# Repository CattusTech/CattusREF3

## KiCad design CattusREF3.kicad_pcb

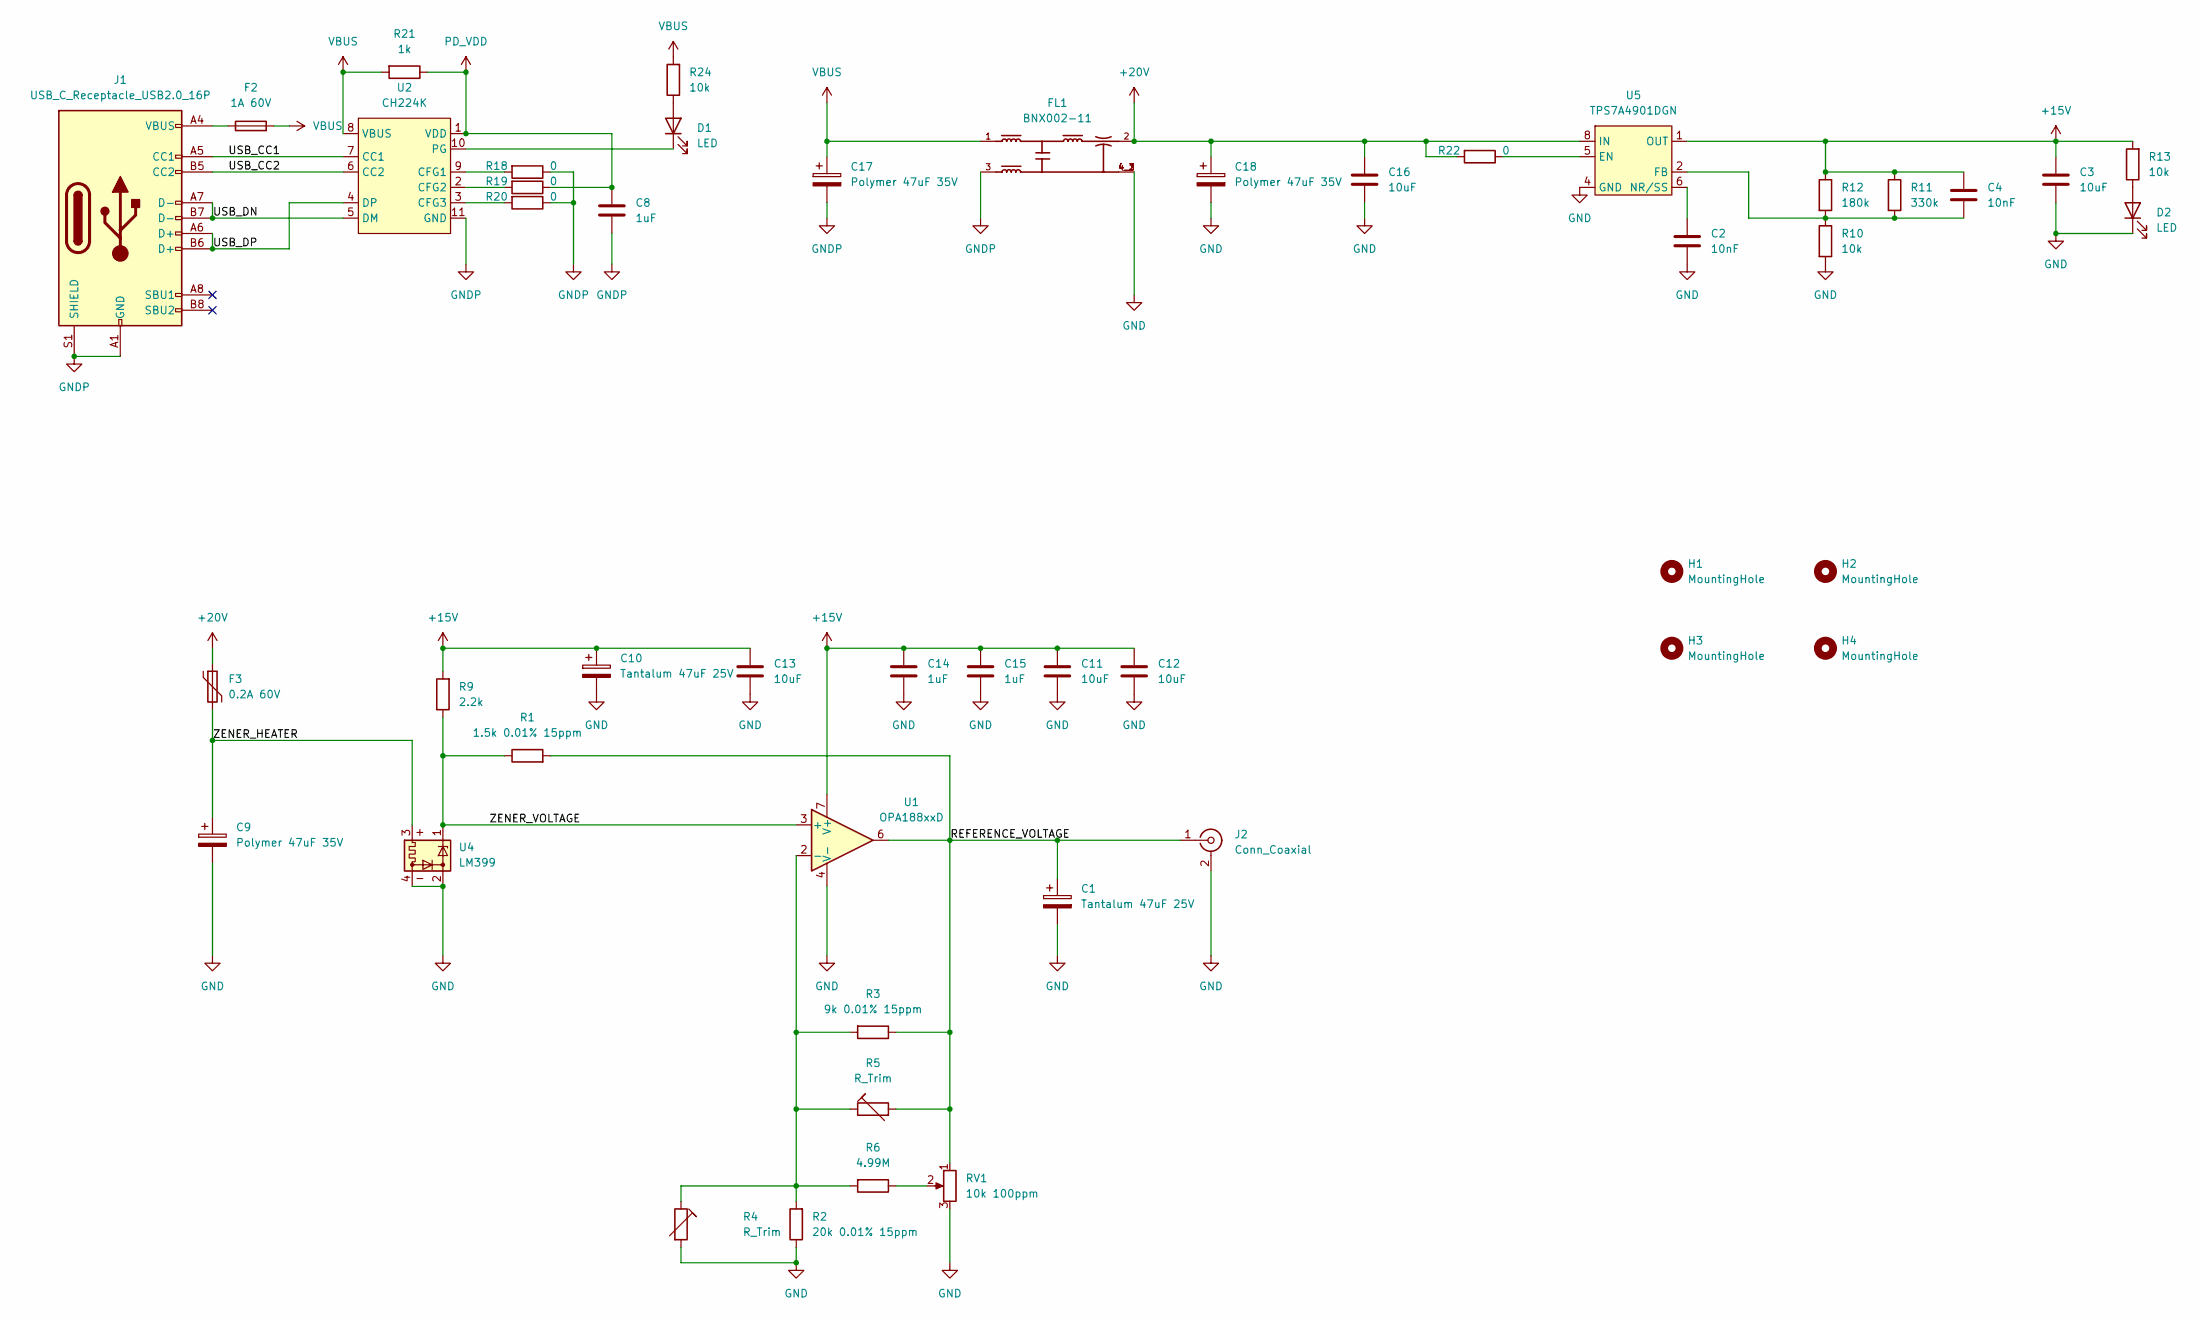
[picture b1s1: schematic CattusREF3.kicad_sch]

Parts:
C1, C10: Tantalum 47uF 25V; CP_EIA-7343-31_Kemet-D
C2, C4: 10nF; C_0603_1608Metric
C3, C11, C12, C13, C16: 10uF; C_0805_2012Metric
C8, C14, C15: 1uF; C_0603_1608Metric
C9, C17, C18: Polymer 47uF 35V; CP_Elec_6.3x7.7
D1, D2: LED; LED_0603_1608Metric
F2: 1A 60V; Fuse_1206_3216Metric
F3: 0.2A 60V; Fuse_1206_3216Metric
FL1: BNX002-11; BNX002; PARTREV N/A
H1, H2, H3, H4: MountingHole; MountingHole_3.2mm_M3_ISO14580
J1: USB_C_Receptacle_USB2.0_16P; USB_C_Receptacle_GCT_USB4105-xx-A_16P_TopMnt_Horizontal
J2: Conn_Coaxial; SMA_Amphenol_901-143_Horizontal
R1: 1.5k 0.01% 15ppm; R_0603_1608Metric
R2: 20k 0.01% 15ppm; R_0603_1608Metric
R3: 9k 0.01% 15ppm; R_0603_1608Metric
R4, R5: R_Trim; R_0603_1608Metric
R6: 4.99M; R_0603_1608Metric
R9: 2.2k; R_0603_1608Metric
R10, R13, R24: 10k; R_0603_1608Metric
R11: 330k; R_0603_1608Metric
R12: 180k; R_0603_1608Metric
R18, R19, R20, R22: 0; R_0603_1608Metric
R21: 1k; R_0603_1608Metric
RV1: 10k 100ppm; Potentiometer_Bourns_3296W_Vertical
U1: OPA188xxD; SOIC-8_3.9x4.9mm_P1.27mm
U2: CH224K; SSOP-10-1EP_3.9x4.9mm_P1mm_EP2.1x3.3mm
U4: LM399; Analog_TO-46-4_ThermalShield
U5: TPS7A4901DGN; Texas_DGN0008B_VSSOP-8-1EP_3x3mm_P0.65mm_EP2x3mm_Mask1.88x1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

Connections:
+15V: C3.2, C4.2, C10.1, C11.2, C12.2, C13.2, C14.2, C15.2, R9.2, R11.1, R12.1, R13.2, U1.7 (V+), U5.1 (OUT)
+20V: C16.2, C18.1, F3.1, FL1.2, R22.2, U5.8 (IN)
/REFERENCE_VOLTAGE: C1.1, J2.1 (In), R1.2, R3.1, R5.2, RV1.1, U1.6
/USB_CC1: J1.A5 (CC1), U2.7 (CC1)
/USB_CC2: J1.B5 (CC2), U2.6 (CC2)
/USB_DN: J1.A7 (D-), J1.B7 (D-), U2.5 (DM)
/USB_DP: J1.A6 (D+), J1.B6 (D+), U2.4 (DP)
/ZENER_HEATER: C9.1, F3.2, U4.3
/ZENER_VOLTAGE: R1.1, R9.1, U1.3 (+), U4.1
GND: C1.2, C2.1, C3.1, C9.2, C10.2, C11.1, C12.1, C13.1, C14.1, C15.1, C16.1, C18.2, D2.1 (K), FL1.4_1, FL1.4_2, FL1.4_3, J2.2 (Ext), R2.1, R4.2, R10.2, RV1.3, U1.4 (V-), U4.2, U4.4, U5.4 (GND), U5.9 (GND)
GNDP: C8.1, C17.2, FL1.3, J1.A1 (GND), J1.A12 (GND), J1.B1 (GND), J1.B12 (GND), J1.S1 (SHIELD), R18.1, R20.1, U2.11 (GND)
unnamed: D1.2 (A), R24.1
unnamed: D1.1 (K), U2.10 (PG)
unnamed: D2.2 (A), R13.1
unnamed: F2.1, J1.A4 (VBUS), J1.A9 (VBUS), J1.B4 (VBUS), J1.B9 (VBUS)
unnamed: R6.1, RV1.2
unnamed: R2.2, R3.2, R4.1, R5.1, R6.2, U1.2 (-)
unnamed: R18.2, U2.9 (CFG1)
unnamed: R19.2, U2.2 (CFG2)
unnamed: R20.2, U2.3 (CFG3)
unnamed: R22.1, U5.5 (EN)
unnamed: C4.1, R10.1, R11.2, R12.2, U5.2 (FB)
unnamed: C2.2, U5.6 (NR/SS)
PD_VDD: C8.2, R19.1, R21.1, U2.1 (VDD)
VBUS: C17.1, F2.2, FL1.1, R21.2, R24.2, U2.8 (VBUS)

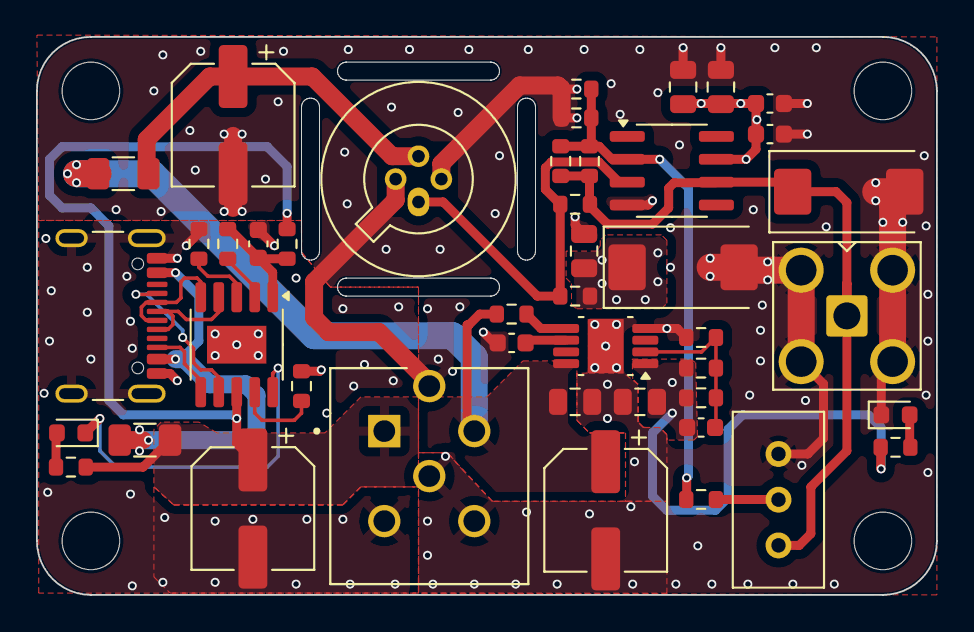
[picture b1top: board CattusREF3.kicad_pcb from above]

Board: 4 copper layers, 50.0 x 31.0 mm, 48 parts (0 on the bottom side), 25 nets.
